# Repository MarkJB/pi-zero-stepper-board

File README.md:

CC BY-NC-SA 2016 Copyright Mark Benson etc etc

This is my vPiP Raspberry Pi Zero board especially for Pi day. vPiP (vertical Pi Plotter) is polargraph style, hanging v plotter.

This is a work in progress and is currently untested.

vPiP is as yet unreleased. More information as it becomes available.

I wouldn't bother making one yet...

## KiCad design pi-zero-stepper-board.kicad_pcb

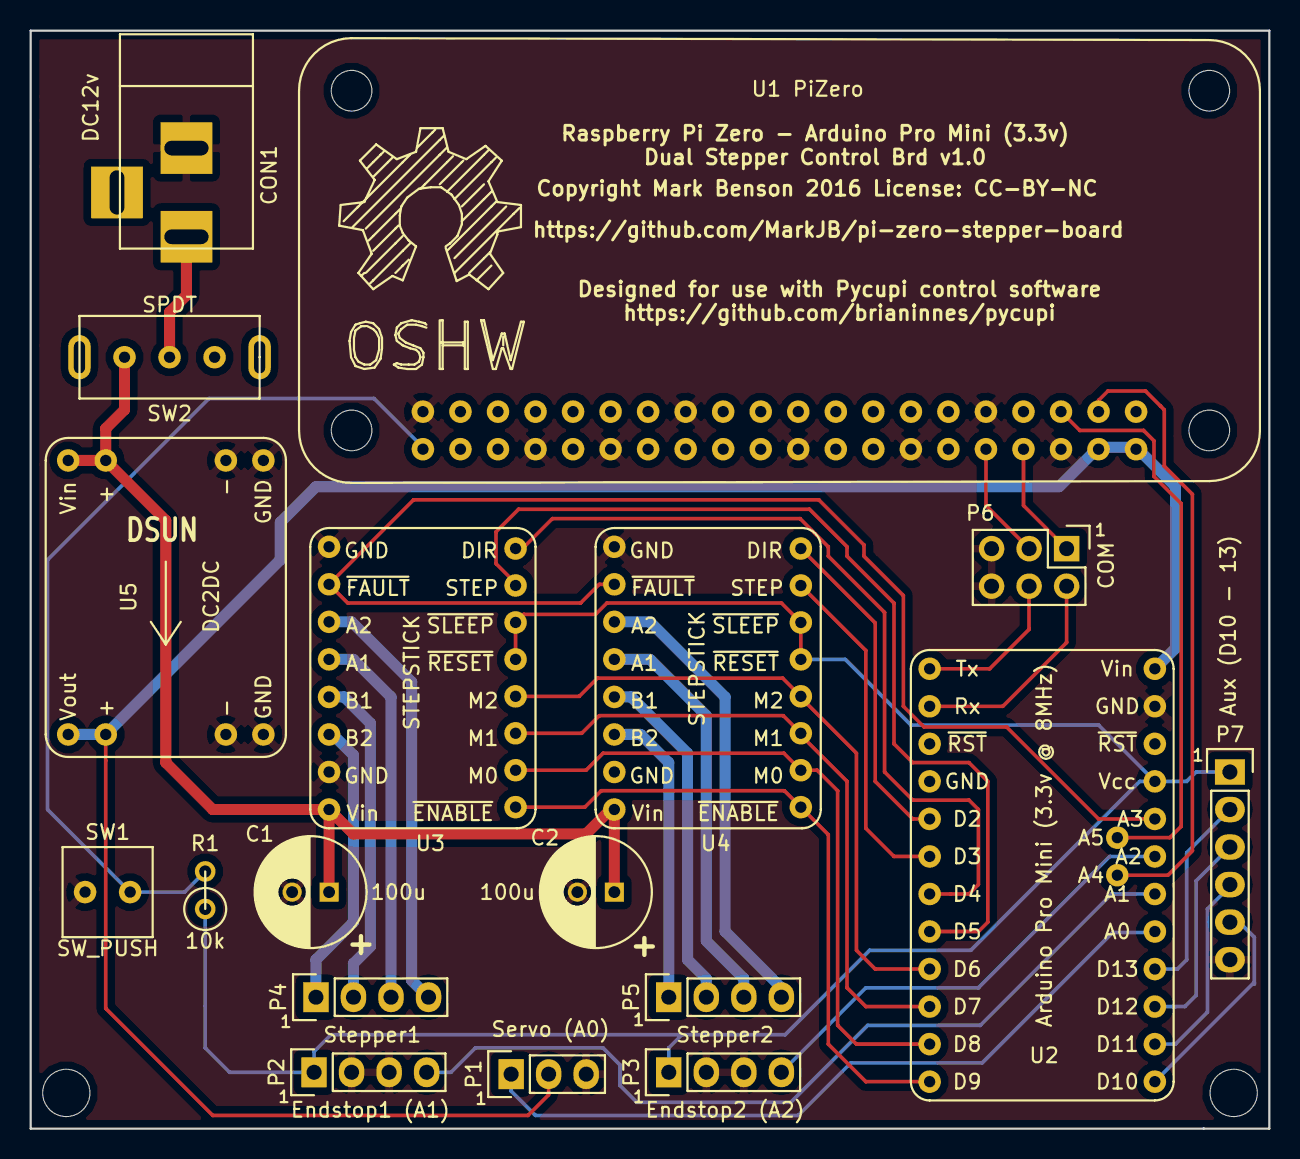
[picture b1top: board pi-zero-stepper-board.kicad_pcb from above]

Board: 2 copper layers, 83.8 x 74.3 mm, 20 parts (0 on the bottom side), 36 nets.

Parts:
C1, C2: 100u; C_Radial_D7.5_L11.2_P2.5
CON1: DC12v; BARREL_JACK
M3_1, M3_2: MountingHole_3.2mm_M3
P1: Servo (A0); Pin_Header_Straight_1x03
P2: Endstop1 (A1); Pin_Header_Straight_1x04
P3: Endstop2 (A2); Pin_Header_Straight_1x04
P4: Stepper1; Pin_Header_Straight_1x04
P5: Stepper2; Pin_Header_Straight_1x04
P6: COM; Pin_Header_Straight_2x03
P7: Aux (D10 - 13); Pin_Header_Straight_1x06
R1: 10k; R1
SW1: SW_PUSH; TactSw
SW2: SPDT; SlideSw
U1: PiZero; Pi_Zero
U2: Arduino_Pro_Mini_3v3_8MHz; Arduino_Pro_Mini
U3, U4: STEPSTICK; Stepstick
U5: DC2DC; DSUN_DC2DC

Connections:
+12V: C1.1, C2.1, SW2.1, U3.8, U4.8, U5.3, U5.4
/3v3: P2.1, P3.1, P7.1, R1.1, U2.21, U3.13, U3.14, U4.13, U4.14
/ArdRx: P6.2, U2.2
/ArdTx: P6.4, U2.1
/D10: P7.2, U2.16
/D11: P7.3, U2.15
/D12: P7.4, U2.14
/D13: P7.5, U2.13
/DIR1: U2.7, U3.16
/DIR2: U2.5, U4.16
/ENABLE: U2.12, U3.9, U4.9
/ESTOP1: P2.4, U2.18
/ESTOP2: P3.4, U2.19
/FAULT: U2.20, U3.2, U4.2
/GPIO21: R1.2, SW1.1, U1.40
/M0: U2.11, U3.10, U4.10
/M1: U2.10, U3.11, U4.11
/M2: U2.9, U3.12, U4.12
/PiRx: P6.3, U1.10
/PiTx: P6.1, U1.8
/SCL: U1.5, U2.26
/SDA: U1.3, U2.25
/SERVO: P1.1, U2.17
/STEP1: U2.8, U3.15
/STEP2: U2.6, U4.15
/VCC: P1.2, U1.2, U1.4, U2.24, U5.5, U5.6
GND: C1.2, C2.2, CON1.2, P1.3, P2.2, P2.3, P3.2, P3.3, P6.5, P6.6, P7.6, SW1.2, U1.6, U1.9, U1.14, U1.20, U1.25, U1.30, U1.34, U1.39, U2.4, U2.23, U3.1, U3.7, U4.1, U4.7, U5.1, U5.2, U5.7, U5.8
unnamed: CON1.1, SW2.2
unnamed: P4.1, U3.6
unnamed: P4.2, U3.5
unnamed: P4.3, U3.4
unnamed: P4.4, U3.3
unnamed: P5.1, U4.6
unnamed: P5.2, U4.5
unnamed: P5.3, U4.4
unnamed: P5.4, U4.3

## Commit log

2016-03-14 :tada: Added .gitattributes & .gitignore files
2016-03-14 Initial commit
    Untested - don't use
2016-03-16 Fixed power track, added I2C and updated brd text
2016-03-28 Added I2C and other fixes

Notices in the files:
pi-zero-stepper-board.kicad_pcb:
Copyright Mark Benson 2016
License: CC-BY-NC
Copyright Mark Benson 2016 License: CC-BY-NC
